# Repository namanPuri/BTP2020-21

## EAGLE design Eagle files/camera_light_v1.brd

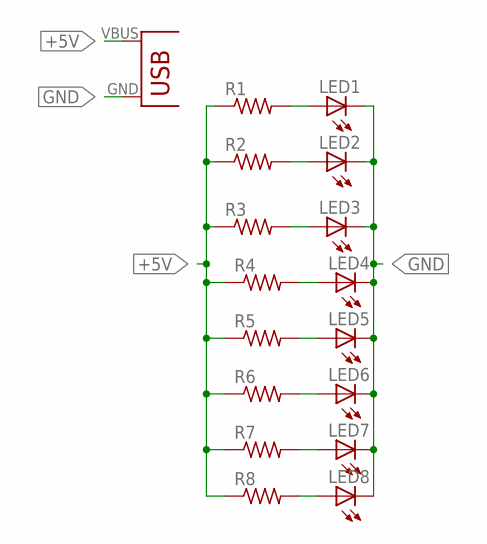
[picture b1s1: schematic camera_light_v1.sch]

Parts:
LED1, LED2, LED3, LED4, LED5, LED6, LED7, LED8: LED1210; EIA1210
R1, R2, R3, R4, R5, R6, R7, R8: RESISTOR0805; R0805
U$1: USB(POWER)

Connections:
+5V: R1.1, R2.1, R3.1, R4.1, R5.1, R6.1, R7.1, R8.1, U$1.VBUS (VCC)
GND: LED1.CATHODE (C), LED2.CATHODE (C), LED3.CATHODE (C), LED4.CATHODE (C), LED5.CATHODE (C), LED6.CATHODE (C), LED7.CATHODE (C), LED8.CATHODE (C), U$1.GND
unnamed: LED1.ANODE (A), R1.2
unnamed: LED2.ANODE (A), R2.2
unnamed: LED3.ANODE (A), R3.2
unnamed: LED4.ANODE (A), R4.2
unnamed: LED5.ANODE (A), R5.2
unnamed: LED6.ANODE (A), R6.2
unnamed: LED7.ANODE (A), R7.2
unnamed: LED8.ANODE (A), R8.2

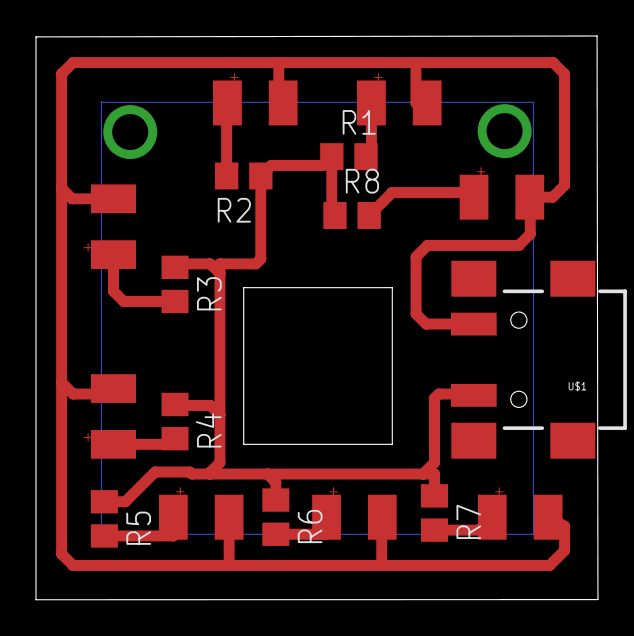
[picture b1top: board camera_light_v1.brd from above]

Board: 2 copper layers, 31.2 x 31.3 mm, 17 parts (0 on the bottom side), 10 nets.

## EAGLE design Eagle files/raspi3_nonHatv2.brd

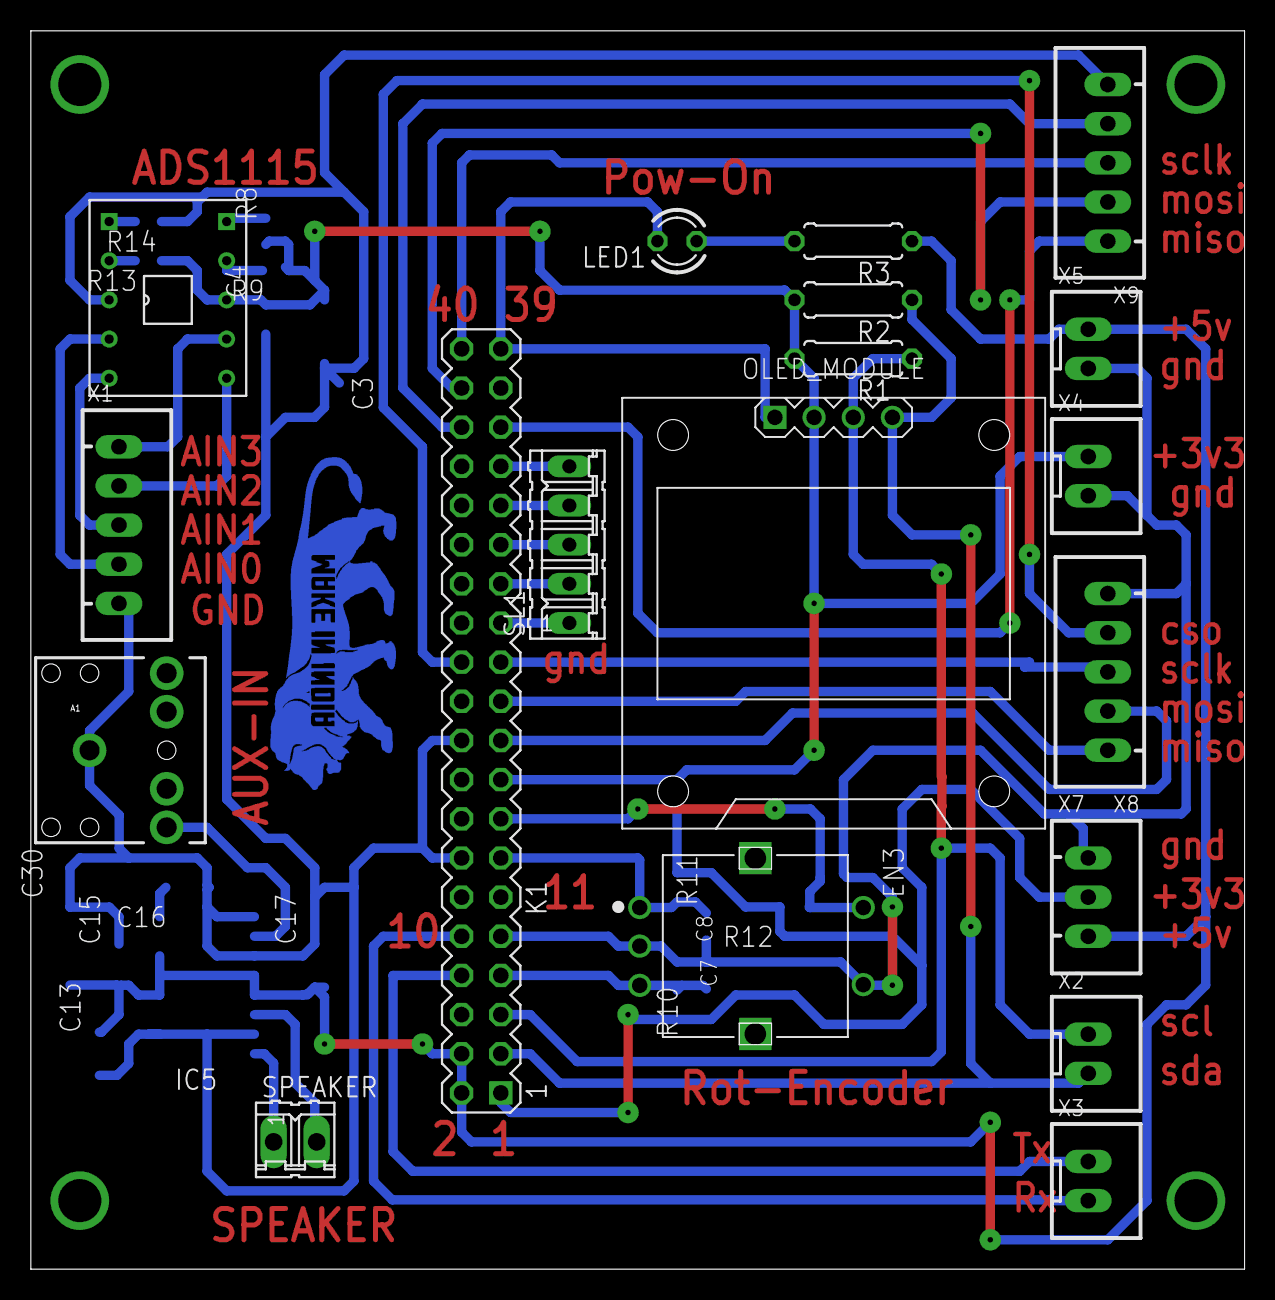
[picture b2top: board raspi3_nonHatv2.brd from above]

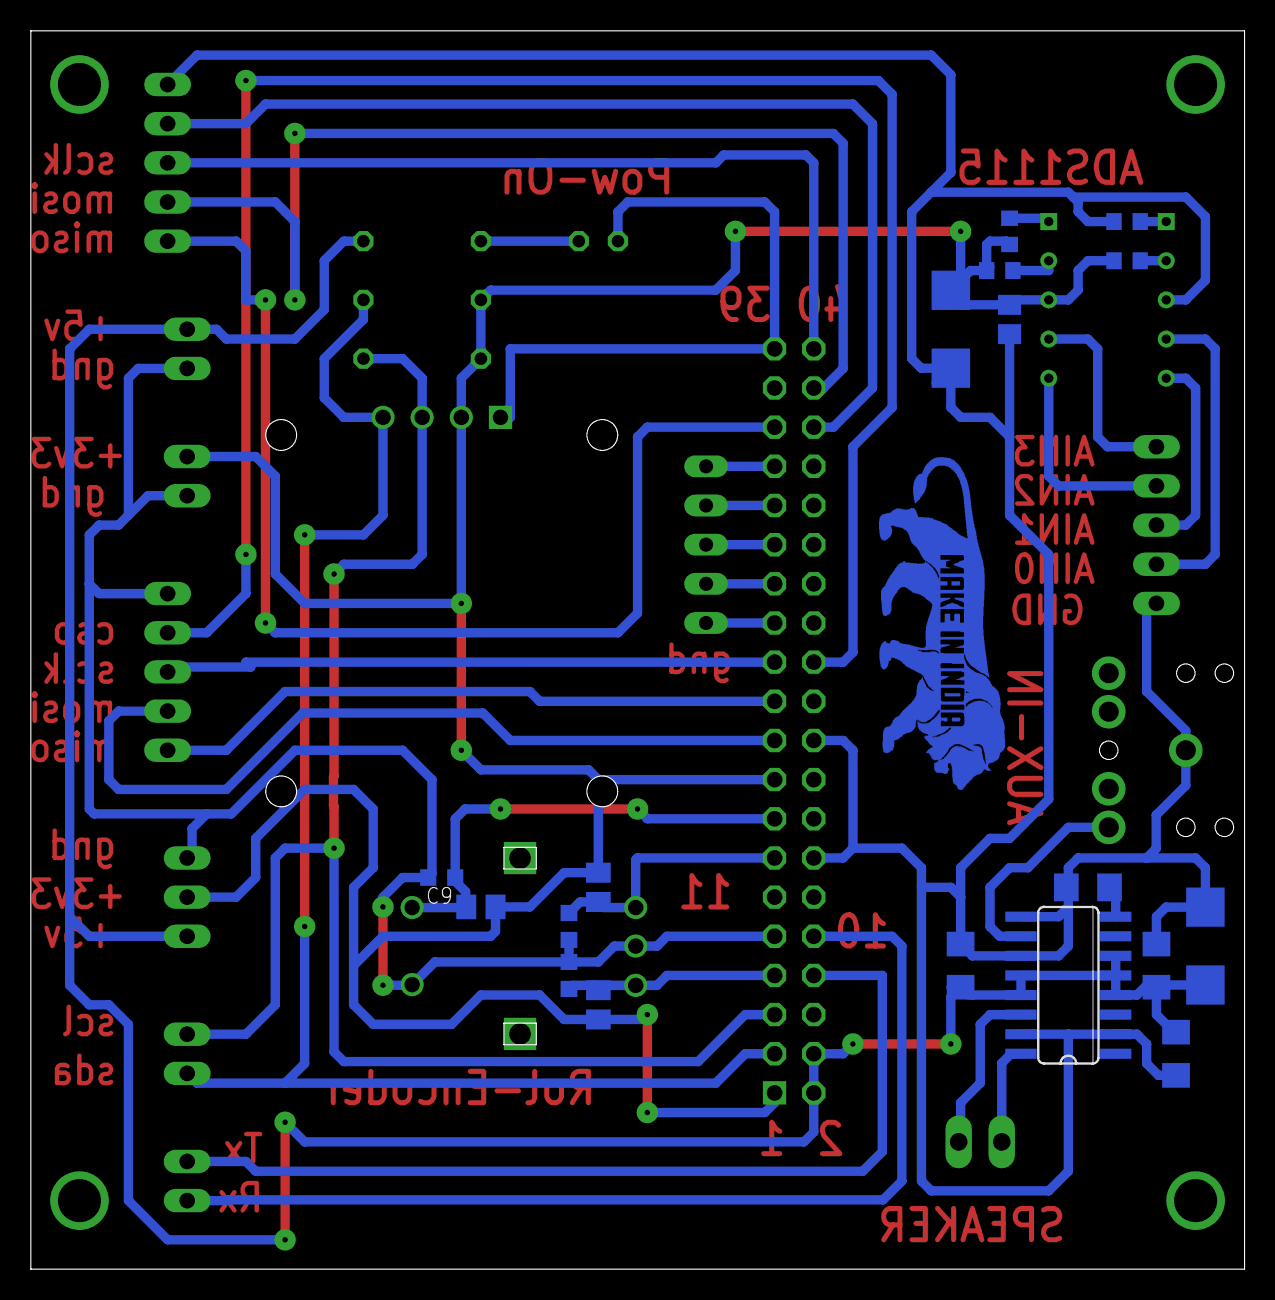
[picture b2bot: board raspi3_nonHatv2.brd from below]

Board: 2 copper layers, 78.7 x 80.3 mm, 38 parts (18 on the bottom side), 35 nets.

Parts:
A1: AUDIO-JACK
C3: 10u; C/6032-28R
C4: 0.1u; C0805
C7, C8, C9: C0603K
C13, C15, C17: 1uf; C1206
C16: 0.1uf; C1206
C30: C/6032-28R
EN3: PEC11L-4220F-S0015
IC5: PAM8403; SOP-16
K1: PIN20X2; PIN_20X2
LED1: LED3MM
OLED_MODULE: DIY-MODULES_DISPLAY-OLED-128X64-I2C
R1, R2, R3: 10k; 0207/7
R8, R9, R13, R14: 10k; R0603
R10, R11, R12: M0805
SL1: 05P
SPEAKER: 02P
U$1: MAKE-IN-INDIA-LOGO; MAKE-IN-INDIA
U$3: BOB_10PIN; BOB10
X1, X8, X9: JST-XH-05-PIN-LONG-PAD; JST-XH-05-PACKAGE-LONG-PAD
X2, X3, X4, X5: JST-XH-02-PIN-LONG-PAD; JST-XH-02-PACKAGE-LONG-PAD
X7: JST-XH-03-PIN-LONG-PAD; JST-XH-03-PACKAGE-LONG-PAD

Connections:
0CS0: K1.24, X8.4
0MISO: K1.21, X8.1
0MOSI: K1.19, X8.2
0SCLK: K1.23, X8.3
1CS0: K1.36, X9.4
1MISO: K1.35, X9.1
1MOSI: K1.38, X9.2
1SCLK: K1.40, X9.3
27: K1.27, SL1.2
29: K1.29, SL1.3
31: K1.31, SL1.4
33: K1.33, SL1.5
+3V3: C3.+, C4.1, K1.1, K1.17, OLED_MODULE.2, R1.2, R2.2, R8.2, R9.2, R10.2, R11.2, R12.1, R13.2, U$3.8, X4.1, X7.2
+5V: C13.1, C15.2, C17.2, C30.+, IC5.4, IC5.5, IC5.6, IC5.12, IC5.13, K1.2, K1.4, R3.1, X5.1, X7.3
AIN0: U$3.4, X1.4
AIN1: U$3.5, X1.3
AIN2: U$3.6, X1.2
AIN3: U$3.7, X1.1
CLK: C7.1, EN3.B, K1.7, R10.1
DT: C8.1, EN3.A, K1.13, R11.1
GND: A1.SLEEVE, C3.-, C4.2, C7.2, C8.2, C9.2, C13.2, C15.1, C16.2, C17.1, C30.-, EN3.2, EN3.C, IC5.2, IC5.9, IC5.11, IC5.15, K1.6, K1.9, K1.14, K1.20, K1.25, K1.30, K1.34, K1.39, LED1.K, OLED_MODULE.1, R14.2, SL1.1, U$3.3, X1.5, X4.2, X5.2, X7.1, X8.5, X9.5
unnamed: LED1.A, R3.2
unnamed: IC5.16, SPEAKER.1
unnamed: R8.1, U$3.10
unnamed: R9.1, U$3.9
unnamed: R13.1, U$3.2
unnamed: R14.1, U$3.1
unnamed: IC5.14, SPEAKER.2
unnamed: A1.TIP, IC5.10
unnamed: C16.1, IC5.8
RX: K1.10, X3.2
SCL: K1.5, OLED_MODULE.3, R1.1, X2.1
SDA: K1.3, OLED_MODULE.4, R2.1, X2.2
SW: C9.1, EN3.1, K1.15, R12.2
TX: K1.8, X3.1

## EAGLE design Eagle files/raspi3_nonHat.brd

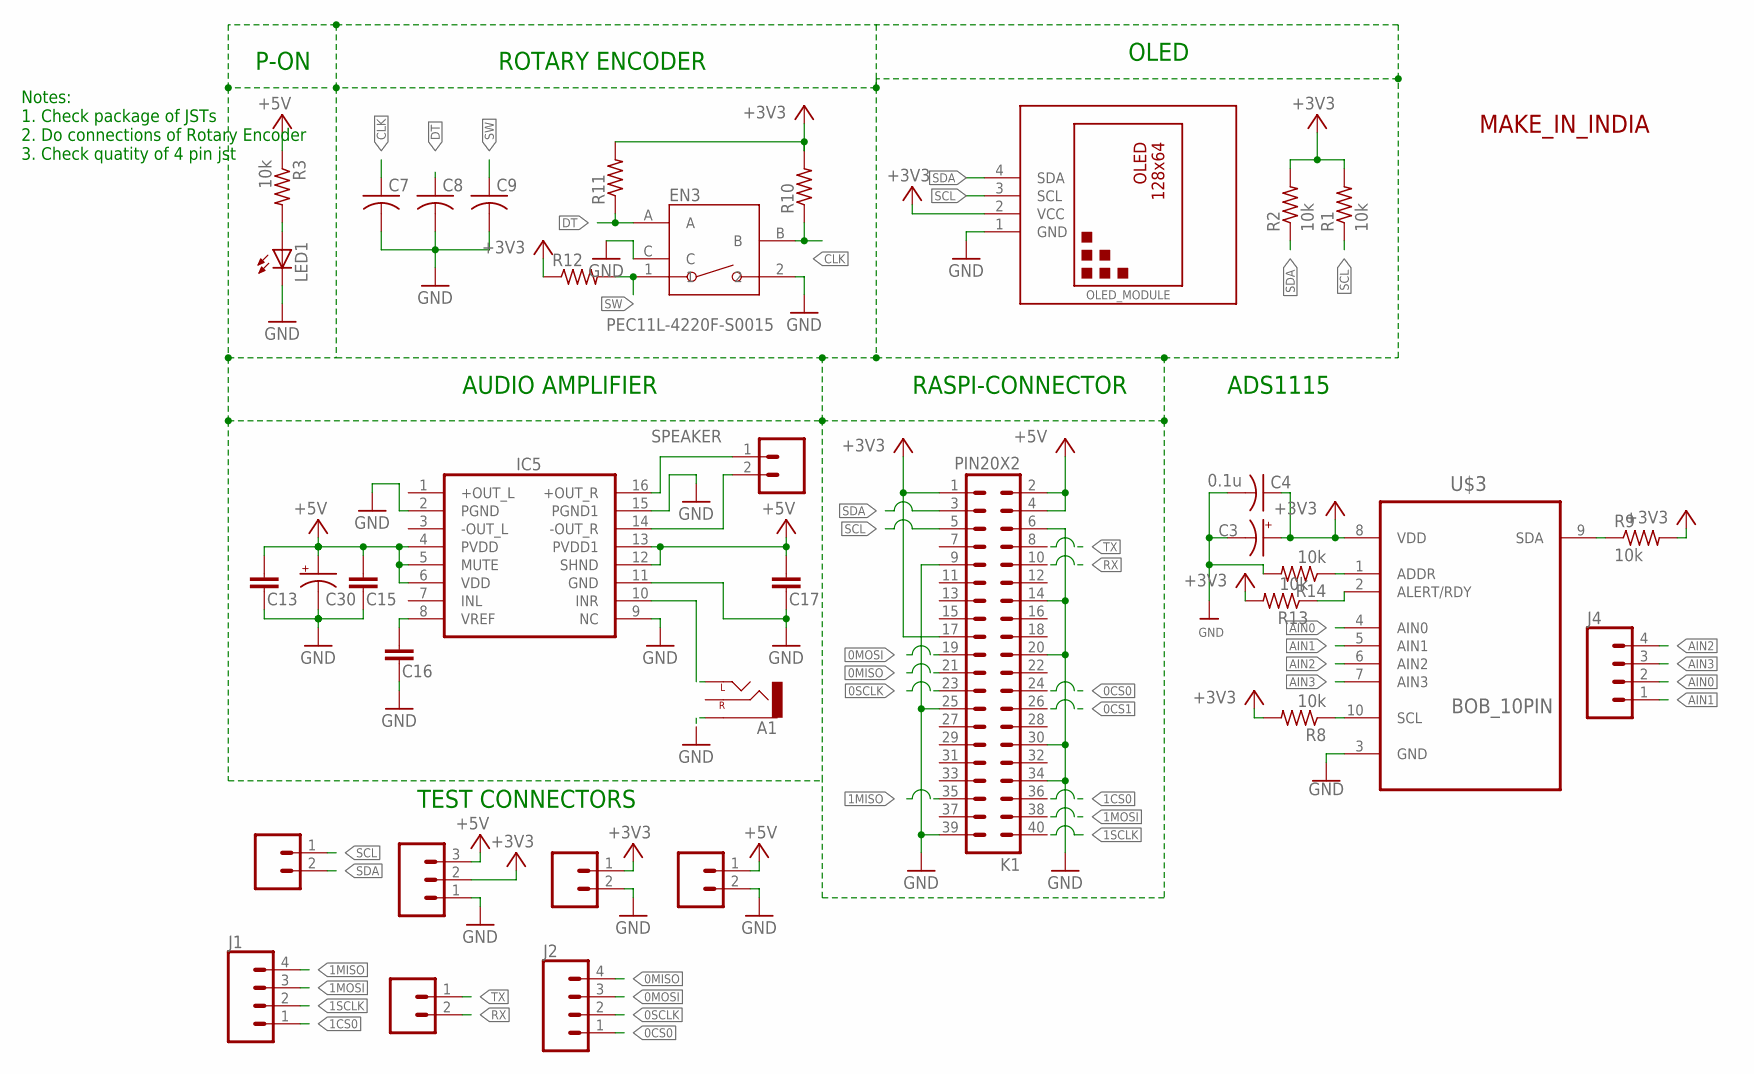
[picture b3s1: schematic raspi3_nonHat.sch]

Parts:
A1: AUDIO-JACKPTH; AUDIO-JACK
C3: 10u; C/6032-28R
C4: 0.1u; C0805
C7, C8, C9: C-USC0603K; C0603K
C13, C15, C17: 1uf; C1206
C16: 0.1uf; C1206
C30: CAP_POL_10V; C/6032-28R
EN3: PEC11L-4220F-S0015
IC5: PAM8403; SOP-16
J1, J2, J4: CONN_04POLAR; MOLEX-1X4
K1: PIN20X2; PIN_20X2
LED1: LED3MM
OLED_MODULE: DIY-MODULES_DISPLAY-OLED-128X64-I2C
POWER: CONN_03POLAR; MOLEX-1X3
R1, R2, R3: 10k; 0207/7
R8, R9, R13, R14: 10k; R0603
R10, R11, R12: R-US_M0805; M0805
SPEAKER: M02; 02P
THERMISTOR1, THERMISTOR2, THERMISTOR3, THERMISTOR4: CONN_02POLAR; MOLEX-1X2
U$1: MAKE-IN-INDIA-LOGO; MAKE-IN-INDIA
U$3: BOB_10PIN; BOB10

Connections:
0CS0: J2.1, K1.24
0CS1: K1.26
0MISO: J2.4, K1.21
0MOSI: J2.3, K1.19
0SCLK: J2.2, K1.23
1CS0: J1.1, K1.36
1MISO: J1.4, K1.35
1MOSI: J1.3, K1.38
1SCLK: J1.2, K1.40
+3V3: C3.+, C4.1, K1.1, K1.17, OLED_MODULE.2 (VCC), POWER.2, R1.2, R2.2, R8.2, R9.2, R10.2, R11.2, R12.1, R13.2, THERMISTOR2.1, U$3.8 (VDD)
+5V: C13.1, C15.2, C17.2, C30.+, IC5.4 (PVDD), IC5.5 (MUTE), IC5.6 (VDD), IC5.12 (SHND), IC5.13 (PVDD1), K1.2, K1.4, POWER.3, R3.1, THERMISTOR3.1
AIN0: J4.2, U$3.4 (AIN0)
AIN1: J4.1, U$3.5 (AIN1)
AIN2: J4.4, U$3.6 (AIN2)
AIN3: J4.3, U$3.7 (AIN3)
CLK: C7.1, EN3.B, R10.1
DT: C8.1, EN3.A, R11.1
GND: A1.SLEEVE, C3.-, C4.2, C7.2, C8.2, C9.2, C13.2, C15.1, C16.2, C17.1, C30.-, EN3.2, EN3.C, IC5.2 (PGND), IC5.9 (NC), IC5.11 (GND), IC5.15 (PGND1), K1.6, K1.9, K1.14, K1.20, K1.25, K1.30, K1.34, K1.39, LED1.K (C), OLED_MODULE.1 (GND), POWER.1, R14.2, THERMISTOR2.2, THERMISTOR3.2, U$3.3 (GND)
unnamed: LED1.A, R3.2
unnamed: IC5.16 (+OUT_R), SPEAKER.1
unnamed: R8.1, U$3.10 (SCL)
unnamed: R9.1, U$3.9 (SDA)
unnamed: R13.1, U$3.2 (ALERT/RDY)
unnamed: R14.1, U$3.1 (ADDR)
unnamed: IC5.14 (-OUT_R), SPEAKER.2
unnamed: A1.TIP (LEFT), IC5.10 (INR)
unnamed: C16.1, IC5.8 (VREF)
RX: K1.10, THERMISTOR4.2
SCL: K1.5, OLED_MODULE.3 (SCL), R1.1, THERMISTOR1.1
SDA: K1.3, OLED_MODULE.4 (SDA), R2.1, THERMISTOR1.2
SW: C9.1, EN3.1, R12.2
TX: K1.8, THERMISTOR4.1

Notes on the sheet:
Notes: 1. Check package of JSTs 2. Do connections of Rotary Encoder 3. Check quatity of 4 pin jst
ROTARY ENCODER
OLED
TEST CONNECTORS
ADS1115
P-ON
AUDIO AMPLIFIER
RASPI-CONNECTOR

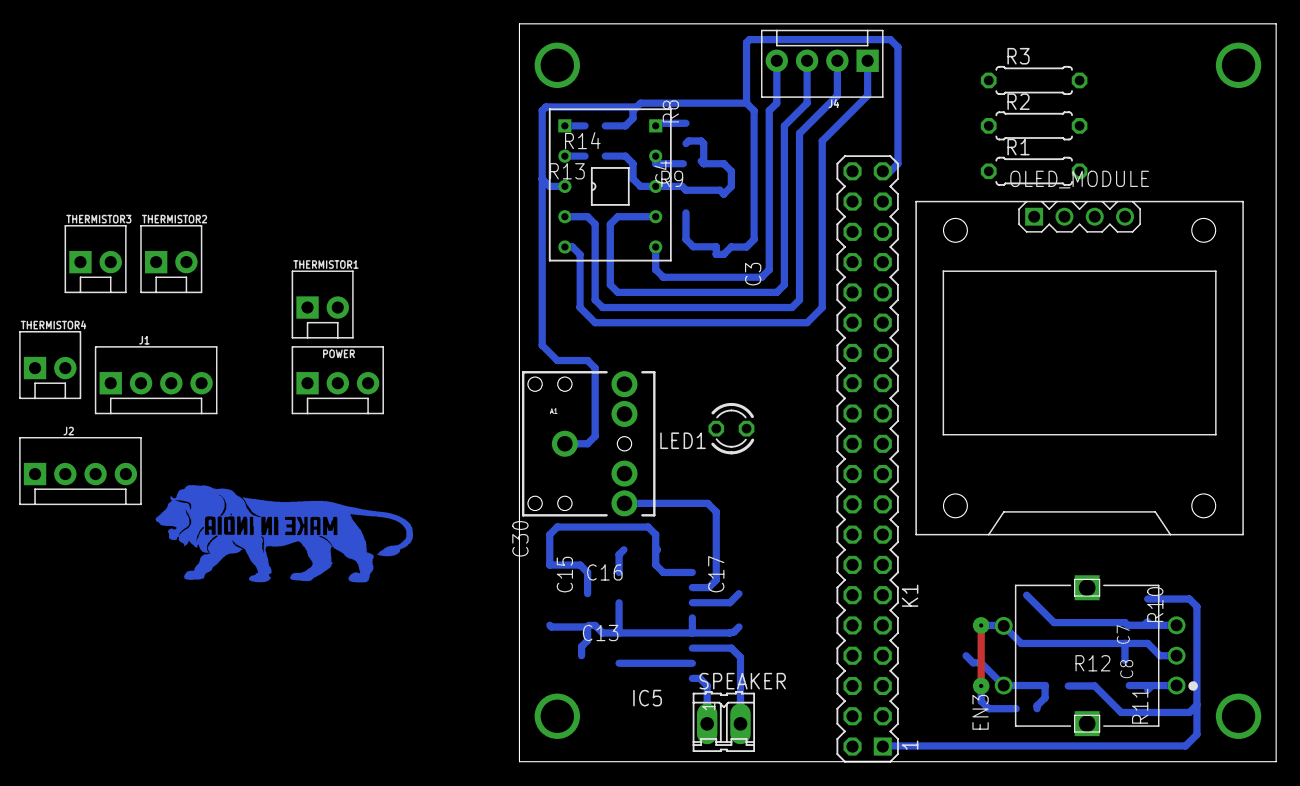
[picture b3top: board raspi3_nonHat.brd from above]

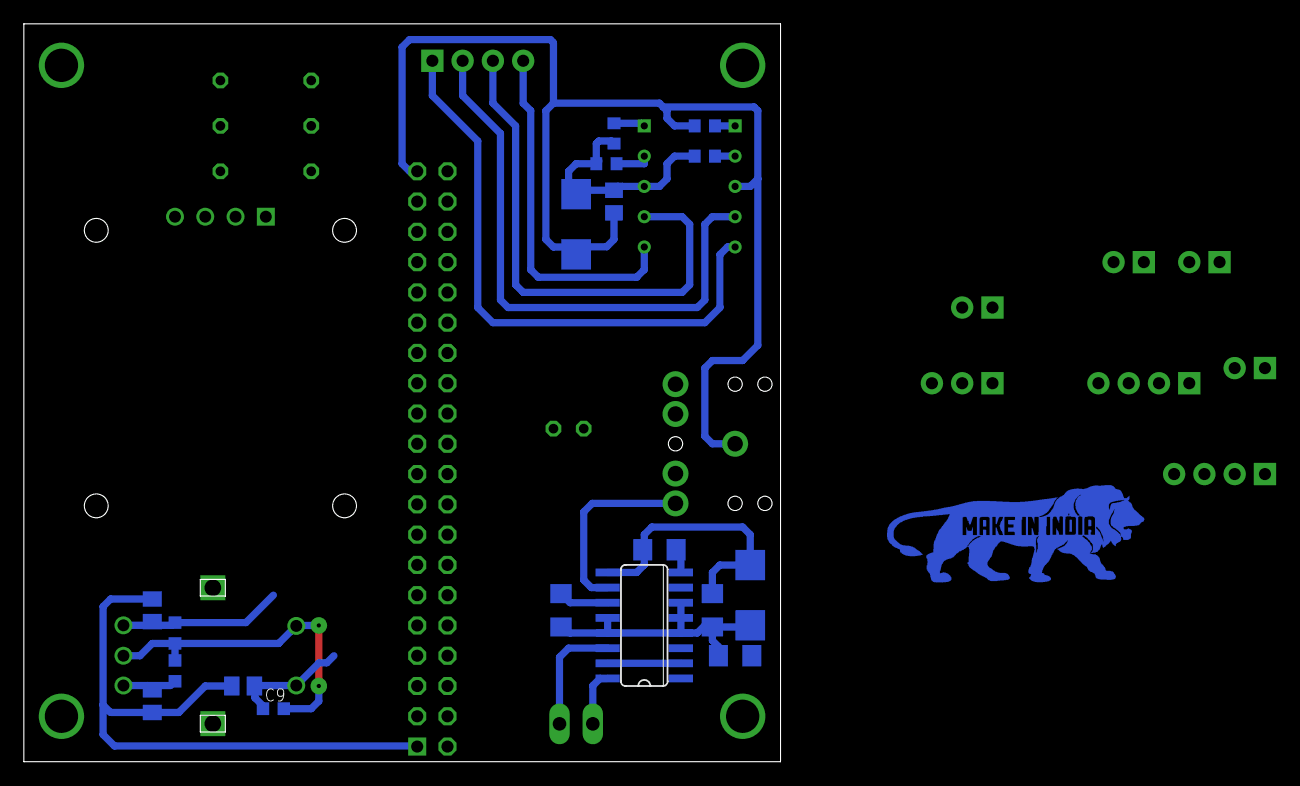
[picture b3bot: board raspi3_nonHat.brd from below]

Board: 2 copper layers, 63.5 x 61.9 mm, 37 parts (18 on the bottom side), 31 nets.

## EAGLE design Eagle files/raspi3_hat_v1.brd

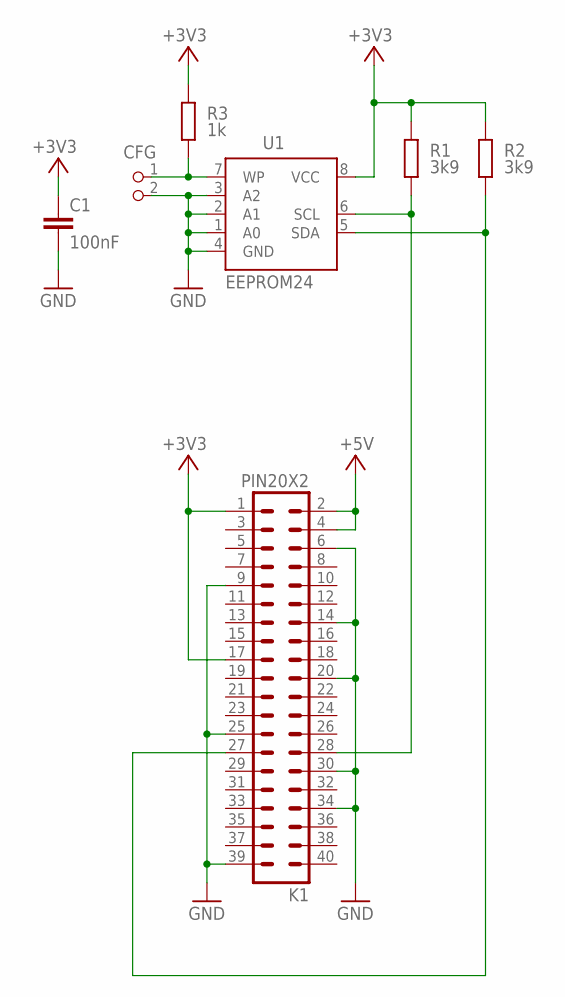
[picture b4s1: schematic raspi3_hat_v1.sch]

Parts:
C1: 100nF; C0805K
CFG: PIN2_100; PIN_W_2
K1: PIN20X2; PIN_20X2
R1, R2: 3k9; M0805; TOLERANCE 5%
R3: 1k; M0805; TOLERANCE 5%
U1: EEPROM24; SOIC8

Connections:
+3V3: C1.1, K1.1, K1.17, R1.2, R2.2, R3.2, U1.8 (VCC)
+5V: K1.2, K1.4
GND: C1.2, CFG.2, K1.6, K1.9, K1.14, K1.20, K1.25, K1.30, K1.34, K1.39, U1.1 (A0), U1.2 (A1), U1.3 (A2), U1.4 (GND)
unnamed: K1.28, R1.1, U1.6 (SCL)
unnamed: K1.27, R2.1, U1.5 (SDA)
unnamed: CFG.1, R3.1, U1.7 (WP)

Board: 2 copper layers, 7 parts (0 on the bottom side), 6 nets, no tracks yet.

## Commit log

2020-09-18 repository created
2020-09-23 audio+butt_1
2020-09-24 color picker sample codes
2020-09-24 hi added
2020-09-24 eagle files added
2020-09-24 clean 1
2020-09-24 code for downloading files
2020-09-28 28-boot
2020-09-30 eagle updated
2020-09-30 eagle up
2020-09-30 30-eagle
2020-09-30 30-eagle2
2020-10-02 added ads1115
2020-10-03 3-Eagle_final
2020-10-03 4-eagle-final
2020-10-04 rearranged
2020-10-04 restored v4
2020-10-05 size adjusted
2020-10-05 5-eagle
2020-10-06 top layer updated
2020-10-08 added library
2020-10-08 8-eagle
2020-10-08 raspi material added
2020-10-09 removed
2020-10-10 colors updated
2020-10-12 colors dwnlded
2020-10-12 color names updated
2020-10-13 sample audio
2020-10-13 audio wave sample
2020-10-13 color program v3
2020-10-14 hindi colors added
2020-10-19 speaking_v2 added
2020-10-19 corrected
2020-10-19 exp with button
2020-10-19 colors csv up
2020-10-19 exp python
2020-10-19 17-oct
2020-10-19 19-color
2020-11-19 19-11-20
2020-11-19 v3_pass
2020-11-19 detector
2020-11-19 number detection sample images added
2020-11-19 v3 take 2
2020-11-19 v3 test
2020-11-20 hsv 1st
2020-11-20 1 day before
2020-11-20 1 day before 2
2020-11-20 1 day bef 3
2020-11-20 1 day b 4
2020-11-20 no. detection
2020-11-21 the day 1
2020-11-21 last day 2
2020-11-21 done 1
2020-11-21 lcd_screen code
2020-11-22 lcd code up
2020-11-23 lcd-up
2020-11-27 images added
2020-11-27 nothing
2020-11-27 tessaract
2020-11-27 tesseract
2020-11-27 images
2020-11-27 images for tess
2020-11-27 new method

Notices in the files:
parts and their libraries:
SparkFun-Connectors: Licensing: Creative Commons ShareAlike 4.0 International - https://creativecommons.org/licenses/by-sa/4.0
